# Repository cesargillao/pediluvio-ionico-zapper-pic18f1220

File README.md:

# Pediluvio Iónico con Zapper (PIC18F1220)

## Se proporciona:
* Diagrama esquemático para emular el funcionamiento (Proteus)
* Diagrama esquemático y PCB (CadSoft Eagle)
* Software en C y ASM con su respectivo HEX (CCS Compiler)

### Si te gusta el proyecto, recomiendo dejar una estrella en el mismo o en mi perfil.
### Eso me inspira a seguir colaborando a la comunidad ❤.

# ⚠ Advertencia ⚠ 
### Este producto no ha sido probado más allá de una emulación mediante software y fue desarrollado con fines educativos. Por lo tanto, el uso que se le quiera dar a este proyecto es responsabilidad de quien lo implemente.

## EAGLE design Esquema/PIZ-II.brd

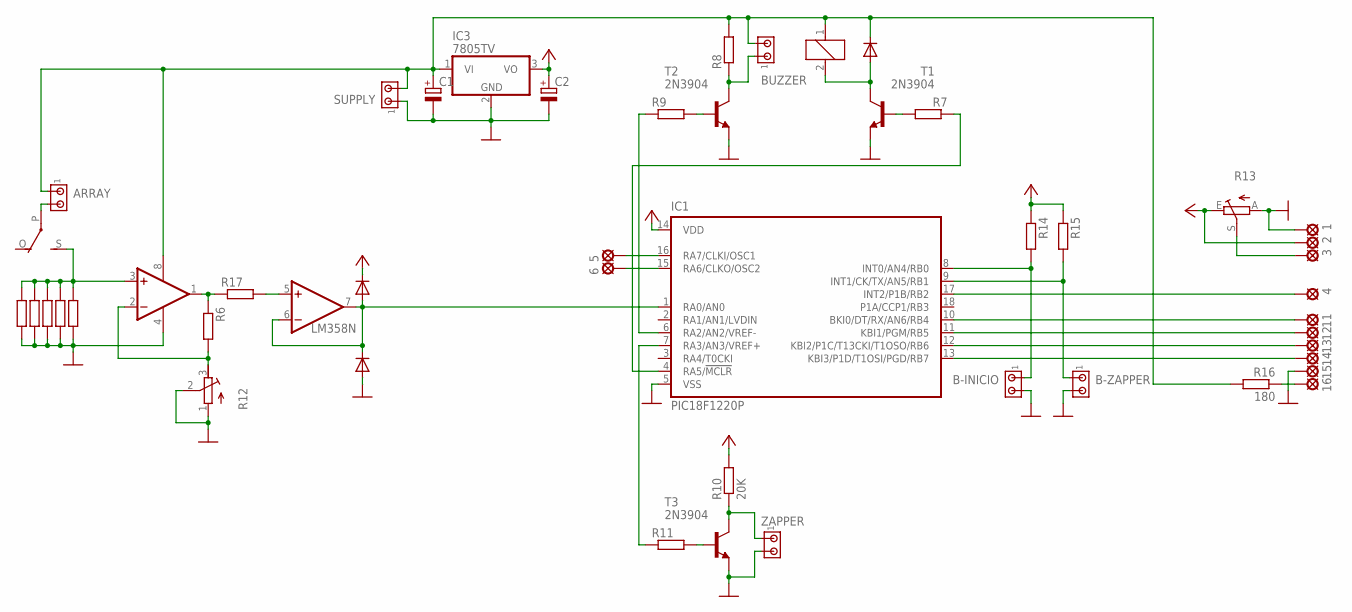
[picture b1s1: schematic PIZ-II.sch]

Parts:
1, 2, 3, 4, 5, 6, 11, 12, 13, 14, 15, 16: LSP10
ARRAY: MTA02-100; 10X02MTA
B-INICIO: MTA02-100; 10X02MTA
B-ZAPPER: MTA02-100; 10X02MTA
BUZZER: MTA02-100; 10X02MTA
C1, C2: CPOL-EUE2.5-7; E2,5-7
D1, D2, D3: 1N4148DO35-7; DO35-7
IC1: PIC18F1220P; DIL18
IC2: LM358N; DIL08
IC3: 7805TV; TO220V
K1: G5L; G5LE
R1, R2, R3, R4, R5, R6, R7, R8, R9, R11, R14, R15, R17: R-EU_0204/7; 0204/7
R10: 20K; 0204/7
R12: R-TRIMM64W; RTRIM64W
R13: TRIM_EU-CA6V; CA6V
R16: 180; 0204/7
SUPPLY: MTA02-100; 10X02MTA
T1, T2, T3: 2N3904; TO92
ZAPPER: MTA02-100; 10X02MTA

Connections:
GND: 1.MP, 15.MP, B-INICIO.2, B-ZAPPER.2, C1.-, C2.-, D2.A, IC1.5 (VSS), IC2.4 (V-), IC3.2 (GND), R1.2, R2.2, R3.2, R4.2, R5.2, R12.1 (A), R12.2 (S), R13.A, SUPPLY.1, T1.3 (E), T2.3 (E), T3.3 (E), ZAPPER.2
unnamed: IC2.3 (+IN), K1.S, R1.1, R2.1, R3.1, R4.1, R5.1
unnamed: ARRAY.2, K1.P
unnamed: IC2.5 (+IN), R17.2
unnamed: IC2.2 (-IN), R6.2, R12.3 (E)
unnamed: BUZZER.1, R8.1, T2.1 (C)
unnamed: D1.A, D2.C, IC1.1 (RA0/AN0), IC2.6 (-IN), IC2.7 (OUT)
unnamed: D3.A, K1.2, T1.1 (C)
unnamed: R10.1, T3.1 (C), ZAPPER.1
unnamed: R7.2, T1.2 (B)
unnamed: R9.2, T2.2 (B)
unnamed: R11.2, T3.2 (B)
unnamed: IC1.6 (RA2/AN2/VREF-), R9.1
unnamed: 4.MP, IC1.17 (INT2/P1B/RB2)
unnamed: IC1.4 (RA5/!MCLR), R7.1
unnamed: 14.MP, IC1.13 (KBI3/P1D/T1OSI/PGD/RB7)
unnamed: 13.MP, IC1.12 (KBI2/P1C/T13CKI/T1OSO/RB6)
unnamed: 12.MP, IC1.11 (KBI1/PGM/RB5)
unnamed: 11.MP, IC1.10 (BKI0/DT/RX/AN6/RB4)
unnamed: IC2.1 (OUT), R6.1, R17.1
unnamed: 5.MP, IC1.16 (RA7/CLKI/OSC1)
unnamed: 6.MP, IC1.15 (RA6/CLKO/OSC2)
unnamed: 3.MP, R13.S
unnamed: B-INICIO.1, IC1.8 (INT0/AN4/RB0), R14.2
unnamed: B-ZAPPER.1, IC1.9 (INT1/CK/TX/AN5/RB1), R15.2
unnamed: 16.MP, R16.1
unnamed: ARRAY.1, BUZZER.2, C1.+, D3.C, IC2.8 (V+), IC3.1 (VI), K1.1, R8.2, R16.2, SUPPLY.2
unnamed: IC1.7 (RA3/AN3/VREF+), R11.1
VCC: 2.MP, C2.+, D1.C, IC1.14 (VDD), IC3.3 (VO), R10.2, R13.E, R14.1, R15.1

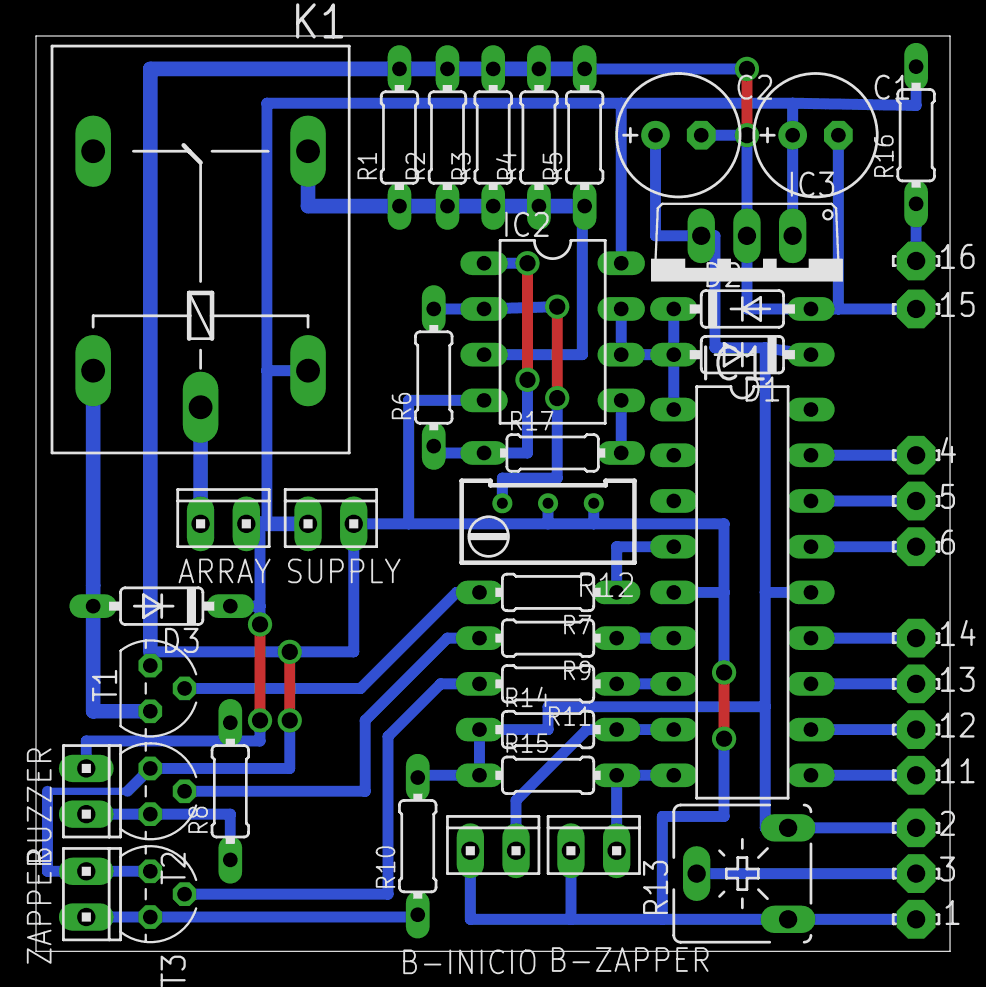
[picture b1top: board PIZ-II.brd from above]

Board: 2 copper layers, 50.8 x 50.9 mm, 47 parts (0 on the bottom side), 29 nets.
